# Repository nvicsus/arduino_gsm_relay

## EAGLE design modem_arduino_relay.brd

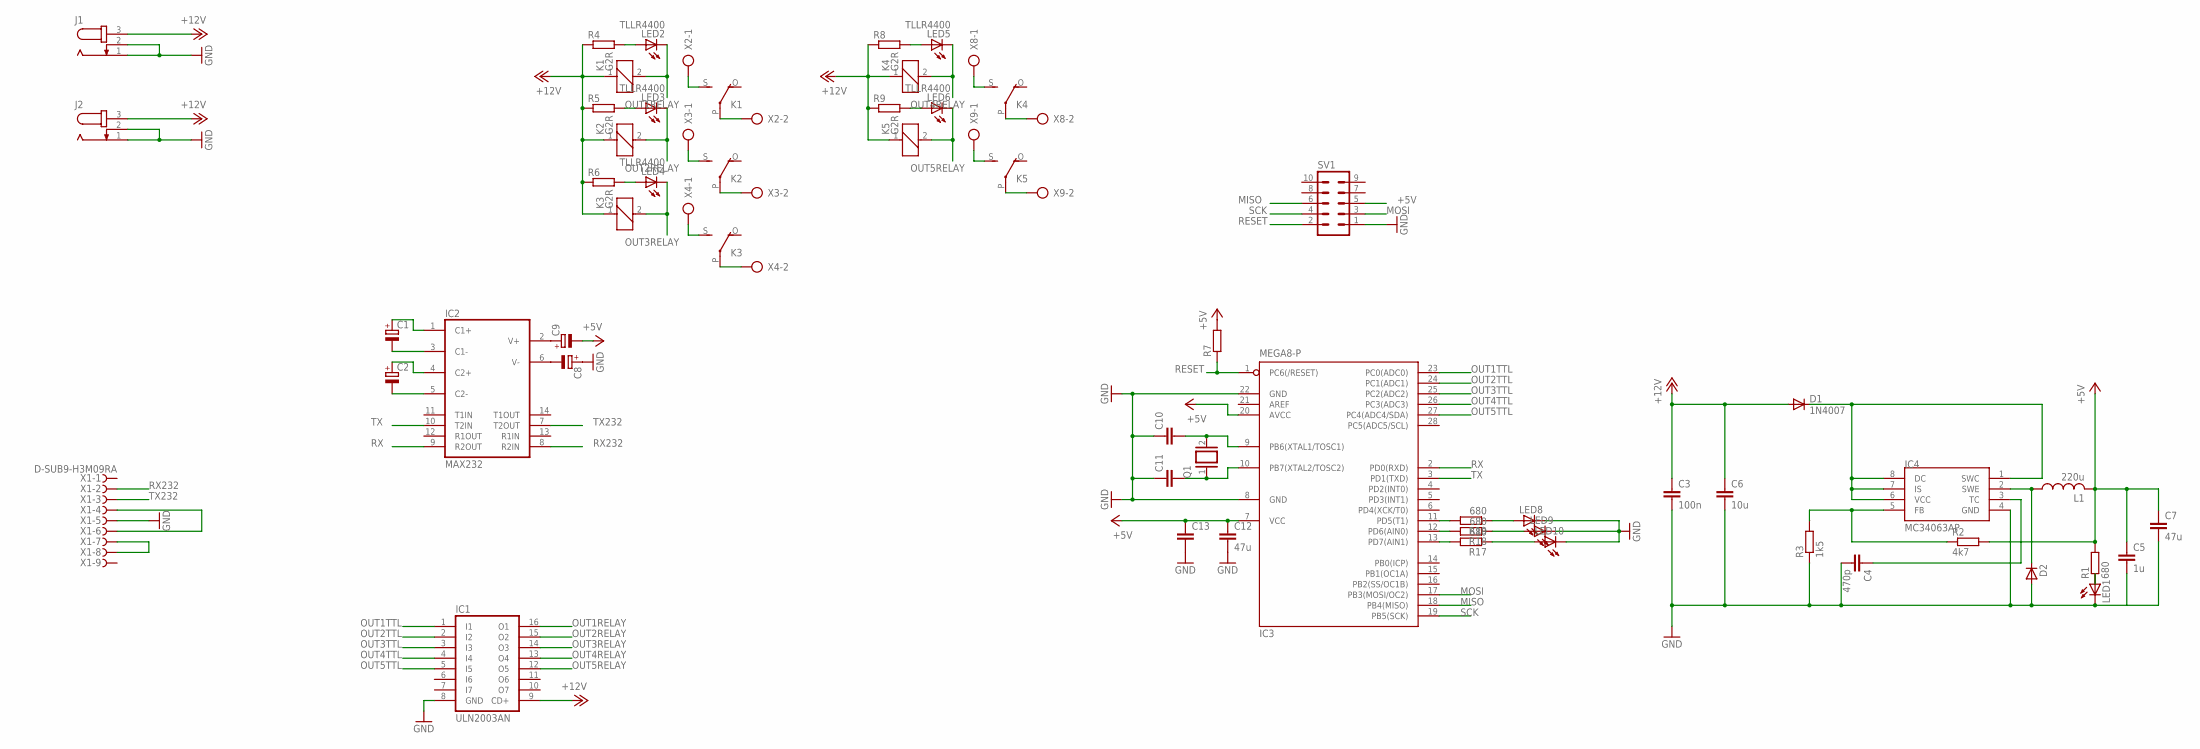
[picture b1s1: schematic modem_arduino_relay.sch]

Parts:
C1, C2, C8, C9: CPOL-EUE2.5-5; E2,5-5
C3: 100n; C1206
C4: 470p; C1206
C5: 1u; C1206
C6: 10u; C050-024X044
C7: 47u; C050-024X044
C10, C11, C13: C-EUC1206; C1206
C12: 47u; C1812
D1: 1N4007; DO41-10
D2: DIODE_E-SMC; DIODE_SMC
IC1: ULN2003AN; DIL16
IC2: MAX232; DIL16
IC3: MEGA8-P; DIL28-3
IC4: MC34063AP; DIL08
J1, J2: JACK-PLUG1; SPC4078
K1, K2, K3, K4, K5: G2R
L1: 220u; TJ3-U1
LED1, LED8, LED9, LED10: LED_ELD260; LED_LD260
LED2, LED3, LED4, LED5, LED6: TLLR4400; LED3MM
Q1: XTAL/S; QS
R1, R17, R18, R19: 680; M1206
R2: 4k7; 0204/7
R3: 1k5; 0204/7
R4, R5, R6, R7, R8, R9: R-EU_M1206; M1206
SV1: MA05-2
X1: D-SUB9-H3M09RA; H3M09RA
X2, X3, X4, X8, X9: AK300/2

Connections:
+5V: C12.1, C13.1, IC3.7 (VCC), IC3.20 (AVCC), R7.2, SV1.5
+12V: C3.1, C6.1, D1.A, IC1.9 (CD+), J1.3, J2.3, K1.1, K2.1, K3.1, K4.1, K5.1, R4.1, R5.1, R6.1, R8.1, R9.1
GND: C3.2, C4.2, C5.2, C6.2, C7.2, C8.+, C10.1, C11.1, C12.2, C13.2, D2.A (C), IC1.8 (GND), IC2.15 (GND), IC3.8 (GND), IC3.22 (GND), IC4.4 (GND), J1.1, J1.2, J2.1, J2.2, LED1.K (C), LED8.K (C), LED9.K (C), LED10.K (C), R3.1, SV1.1, X1.5
MISO: IC3.18 (PB4(MISO)), SV1.6
MOSI: IC3.17 (PB3(MOSI/OC2)), SV1.3
unnamed: C1.+, IC2.1 (C1+)
unnamed: C1.-, IC2.3 (C1-)
unnamed: C2.+, IC2.4 (C2+)
unnamed: C2.-, IC2.5 (C2-)
unnamed: D1.C, IC4.1 (SWC), IC4.6 (VCC), IC4.7 (IS), IC4.8 (DC)
unnamed: LED1.A, R1.1
unnamed: IC4.5 (FB), R2.1, R3.2
unnamed: C4.1, IC4.3 (TC)
unnamed: D2.C (A), IC4.2 (SWE), L1.1
unnamed: C8.-, IC2.6 (V-)
unnamed: C9.+, IC2.2 (V+)
unnamed: C11.2, IC3.10 (PB7(XTAL2/TOSC2)), Q1.1
unnamed: K1.S, X2.1
unnamed: K1.P, X2.2
unnamed: C10.2, IC3.9 (PB6(XTAL1/TOSC1)), Q1.2
unnamed: K2.P, X3.2
unnamed: K2.S, X3.1
unnamed: K3.S, X4.1
unnamed: K3.P, X4.2
unnamed: LED2.A, R4.2
unnamed: LED4.A, R6.2
unnamed: LED3.A, R5.2
unnamed: K4.S, X8.1
unnamed: K4.P, X8.2
unnamed: K5.P, X9.2
unnamed: K5.S, X9.1
unnamed: IC3.11 (PD5(T1)), R19.2
unnamed: IC3.12 (PD6(AIN0)), R18.2
unnamed: IC3.13 (PD7(AIN1)), R17.2
unnamed: LED8.A, R19.1
unnamed: LED9.A, R18.1
unnamed: LED10.A, R17.1
unnamed: X1.7, X1.8
unnamed: X1.4, X1.6
unnamed: LED5.A, R8.2
unnamed: LED6.A, R9.2
OUT1RELAY: IC1.16 (O1), K1.2, LED2.K (C)
OUT1TTL: IC1.1 (I1), IC3.23 (PC0(ADC0))
OUT2RELAY: IC1.15 (O2), K2.2, LED3.K (C)
OUT2TTL: IC1.2 (I2), IC3.24 (PC1(ADC1))
OUT3RELAY: IC1.14 (O3), K3.2, LED4.K (C)
OUT3TTL: IC1.3 (I3), IC3.25 (PC2(ADC2))
OUT4RELAY: IC1.13 (O4), K4.2, LED5.K (C)
OUT4TTL: IC1.4 (I4), IC3.26 (PC3(ADC3))
OUT5RELAY: IC1.12 (O5), K5.2, LED6.K (C)
OUT5TTL: IC1.5 (I5), IC3.27 (PC4(ADC4/SDA))
RESET: IC3.1 (PC6(/RESET)), R7.1, SV1.2
RX: IC2.9 (R2OUT), IC3.2 (PD0(RXD))
RX232: IC2.8 (R2IN), X1.2
SCK: IC3.19 (PB5(SCK)), SV1.4
TX: IC2.10 (T2IN), IC3.3 (PD1(TXD))
TX232: IC2.7 (T2OUT), X1.3
VCC: C5.1, C7.1, C9.-, IC2.16 (VCC), L1.2, R1.2, R2.2

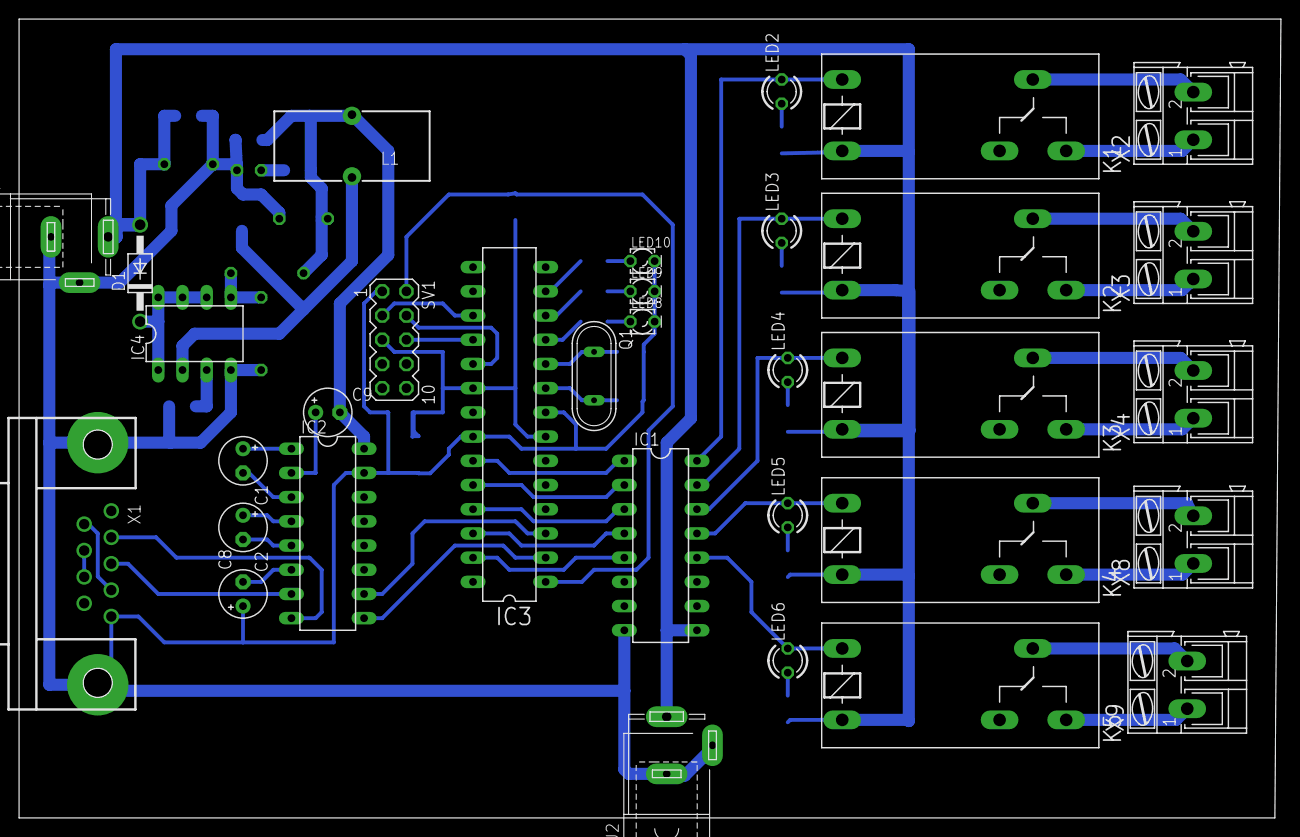
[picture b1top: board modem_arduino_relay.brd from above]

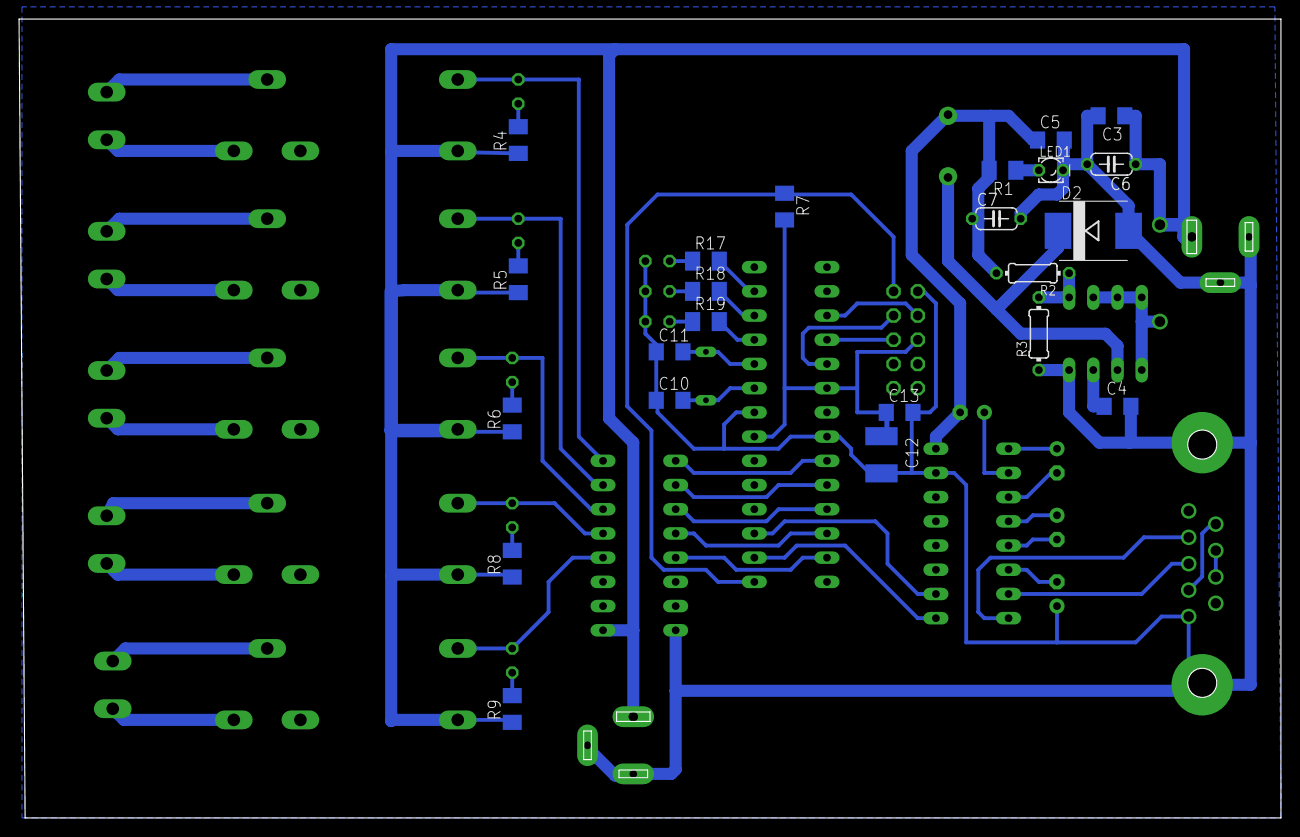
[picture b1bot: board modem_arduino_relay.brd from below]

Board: 2 copper layers, 132.4 x 83.8 mm, 56 parts (23 on the bottom side), 58 nets.

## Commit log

2018-06-11 just commit
